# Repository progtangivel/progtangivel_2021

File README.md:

# progtangivel_2021

Programação tangível é uma solução formada por peças que representam “pedaços” de código. Uma vez encaixadas, elas formam comandos que são executados por um robô ou computador. Ela permite que a programação seja manuseada, facilitando o processo didático.

Propomos o desenvolvimento de um projeto de programação tangível de baixo custo que possa ser acessado e reproduzido de forma aberta em qualquer lugar do país. Além disso, as ex-alunas Camila Farias (IME 09) e Lea Veras (IME 07), que lideram o projeto e são especialistas em educação, vão orientar o projeto no sentido de adequá-lo para o uso em um currículo alinhado com a BNCC e levando em consideração questões de acessibilidade (para estudantes portadores de deficiências).

Como resultado, vamos produzir um modelo para impressão em cortadora a laser e o código de programação, que serão disponibilizados gratuitamente. Dessa forma, educadores que quiserem utilizar essa ferramenta poderão acessar esse recurso de forma livre, precisando apenas adicionar os componentes eletrônicos. Esse projeto também poderá ser utilizado por iniciativas de alunos que queiram montar workshops e outras experiências educacionais como ação social.

## Alunos do IME Participantes:

Ana Luíza Buse Da Silva (IME 22 - Engenharia Elétrica)

Clarice Garnica Barros (IME 23 - Engenharia Química)

Yu Yi Wang Xia (IME 23 - Engenharia de Comunicações)

## Descritivo dos diretórios do projeto

### ArquivosMontagemCaixa 
Aqui se encontram os arquivos do CAD pra montagem da caixa leitora e um pequeno tutorial para montagem das peças e da caixa

### CodigoProcessamentoTangivel 

Aqui de fato se encontra o codigo .ino utilizado para ler e processar o codigo tangível

### CodigoTags 

Este diretório constitui arquivos .ino auxiliares pra formatar e cadastrar as tags tangíveis a serem utilizadas.

### libraries 

Neste diretório, encontram-se todas as bibliotecas que precisam ser importadas (basta importar essas bibliotecas na pasta libraries do Arduino) para funcionar o código.

Nesta pasta, está incluso também as duas bibiliotecas criadas ao longo do projeto:

**TangibleProcessTag.h**

**TangibleActions.h**

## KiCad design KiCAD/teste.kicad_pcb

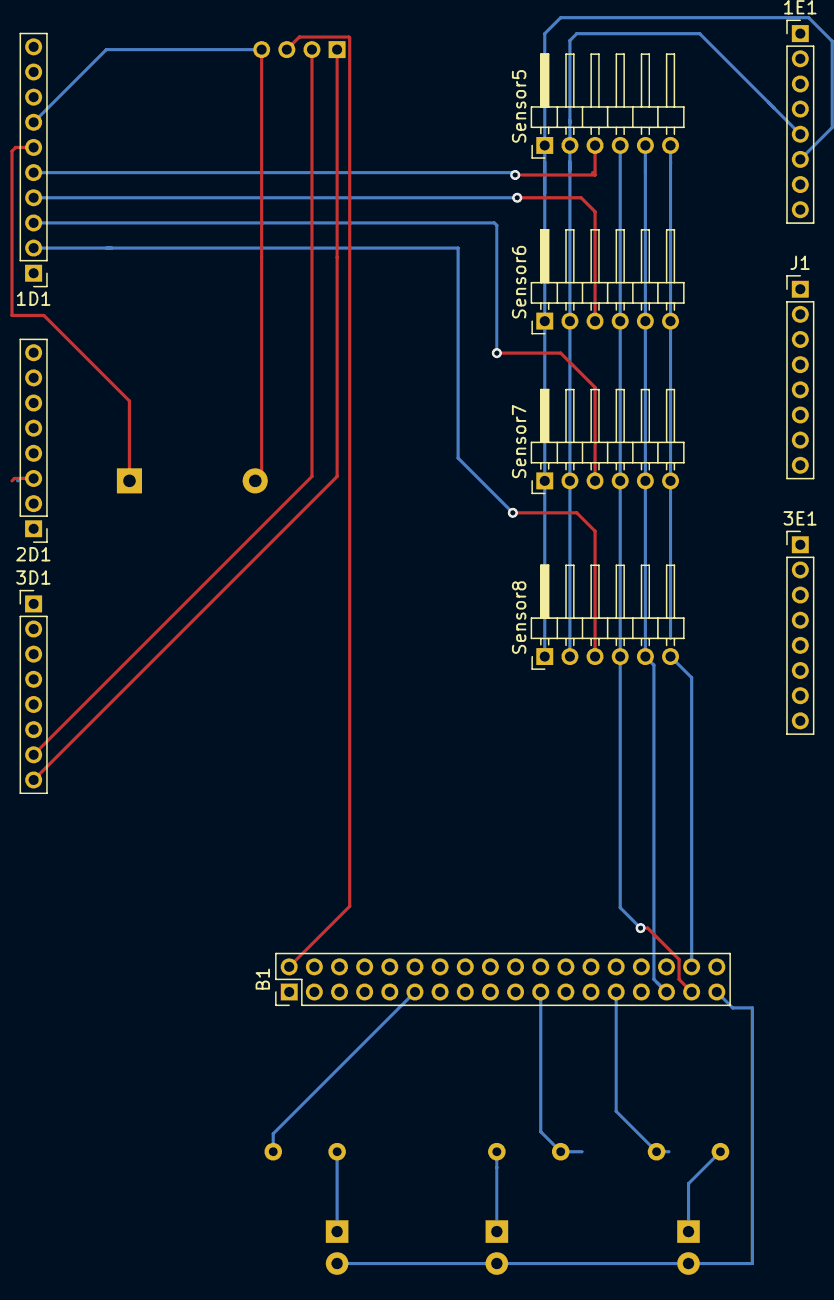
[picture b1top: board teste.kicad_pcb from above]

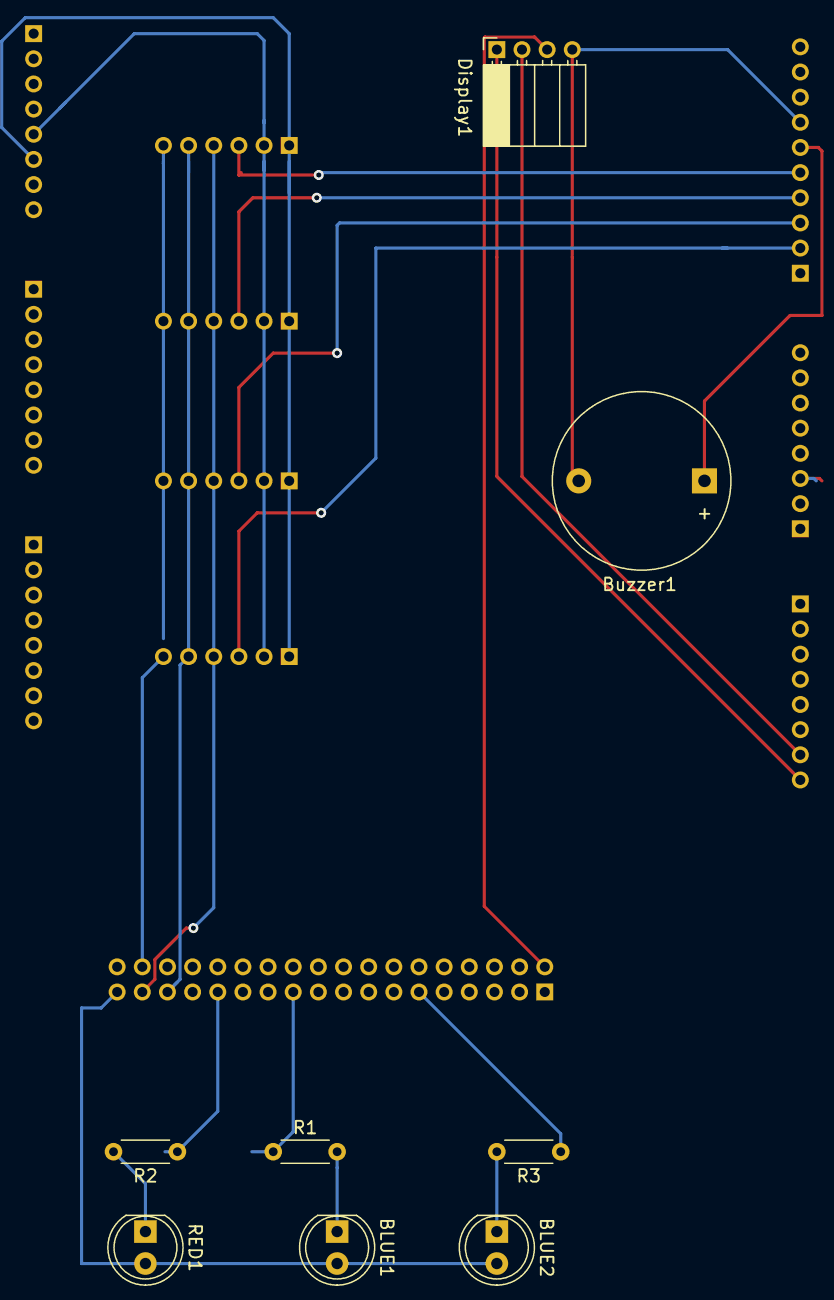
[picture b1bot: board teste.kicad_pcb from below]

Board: 2 copper layers, 19 parts (8 on the bottom side), 22 nets.

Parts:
1D1: Conn_01x10; PinHeader_1x10_P2.00mm_Vertical
1E1, 2D1, 3D1, 3E1: Conn_01x08; PinHeader_1x08_P2.00mm_Vertical
B1: Conn_02x18_Odd_Even; PinHeader_2x18_P2.00mm_Vertical
BLUE1, BLUE2: LED; LED_D5.0mm
Buzzer1: Buzzer; Buzzer_D14mm_H7mm_P10mm
Display1: .; PinSocket_1x04_P2.00mm_Horizontal
J1: Conn_01x08; PinHeader_1x08_P2.00mm_Vertical
R1, R2, R3: 220; R_Axial_DIN0204_L3.6mm_D1.6mm_P5.08mm_Horizontal
RED1: LED; LED_D5.0mm
Sensor5: Sensor 4; PinHeader_1x06_P2.00mm_Horizontal
Sensor6: Sensor 3; PinHeader_1x06_P2.00mm_Horizontal
Sensor7: Sensor 2; PinHeader_1x06_P2.00mm_Horizontal
Sensor8: Sensor 1; PinHeader_1x06_P2.00mm_Horizontal

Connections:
5V: 1E1.5, Sensor5.2, Sensor6.2, Sensor7.2, Sensor8.2
/13: 1D1.6, Buzzer1.1
/20: 3D1.7, Display1.2
/21: 3D1.8, Display1.1
GND: 1E1.6, Sensor5.1, Sensor6.1, Sensor7.1, Sensor8.1
MOSI: B1.33, Sensor5.4, Sensor6.4, Sensor7.4, Sensor8.4
unnamed: 1D1.7, Buzzer1.2, Display1.4
unnamed: B1.2, Display1.3
unnamed: B1.11, R3.1
unnamed: B1.21, R1.1
unnamed: B1.27, R2.1
unnamed: B1.31, Sensor5.5, Sensor6.5, Sensor7.5, Sensor8.5
unnamed: B1.34, Sensor8.6
unnamed: B1.35, BLUE1.2, BLUE2.2, RED1.2
unnamed: BLUE1.1, R1.2
unnamed: BLUE2.1, R3.2
unnamed: R2.2, RED1.1
unnamed: Sensor5.6, Sensor6.6, Sensor7.6
SS-sensor1: 1D1.2, Sensor8.3
SS-sensor2: 1D1.3, Sensor7.3
SS-sensor3: 1D1.4, Sensor6.3
SS-sensor4: 1D1.5, Sensor5.3

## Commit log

2021-11-07 Added KiCAD files to project
2021-11-07 Addded drawio files and assembly tutorial files
2021-11-07 Changed folders setup
2021-11-07 Added Project Libraries
2021-11-07 Added ProcessTag file
2021-11-07 Added Tags files + Changes folder structure
